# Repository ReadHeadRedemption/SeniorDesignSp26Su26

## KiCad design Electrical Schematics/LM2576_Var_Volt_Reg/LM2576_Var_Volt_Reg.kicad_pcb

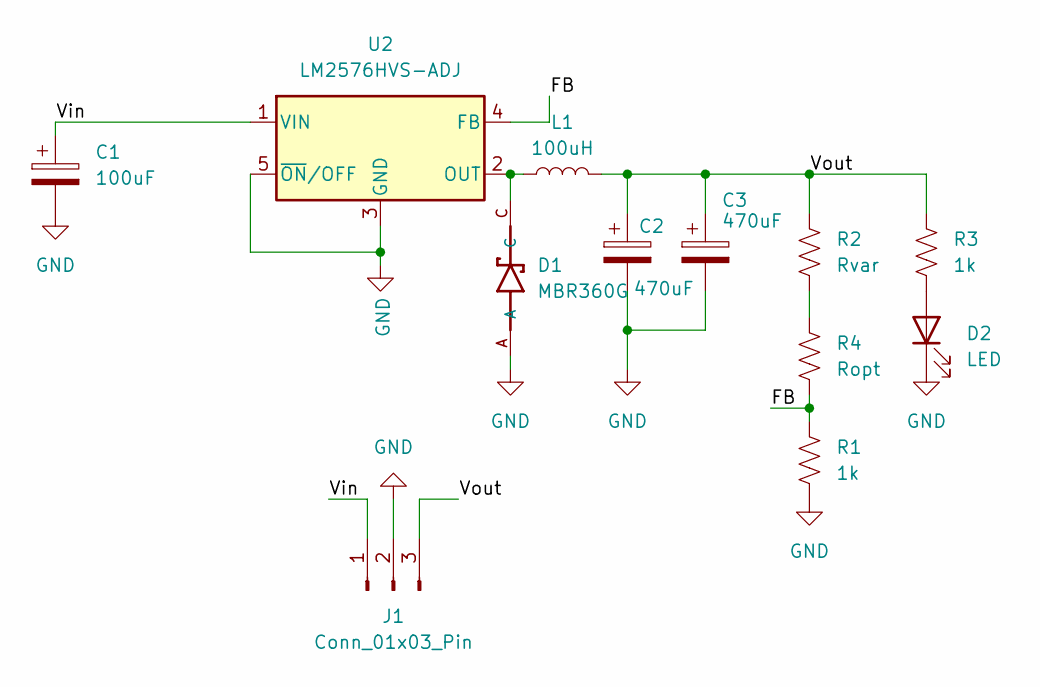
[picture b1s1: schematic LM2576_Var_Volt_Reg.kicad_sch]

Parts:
C1: 100uF; CP_Radial_D6.3mm_P2.50mm
C2, C3: 470uF; CP_Radial_D7.5mm_P2.50mm
D1: MBR360G; DIOAD950W125L840D505
D2: LED; LED_0805_2012Metric_Pad1.15x1.40mm_HandSolder
J1: Conn_01x03_Pin; PinSocket_1x03_P2.54mm_Vertical
L1: 100uH; L_Toroid_Vertical_L21.6mm_W9.5mm_P7.11mm_Pulse_C
R1: 1k; R_1206_3216Metric
R2: Rvar; R_1206_3216Metric_Pad1.30x1.75mm_HandSolder
R3: 1k; R_1206_3216Metric_Pad1.30x1.75mm_HandSolder
R4: Ropt; R_1206_3216Metric_Pad1.30x1.75mm_HandSolder
U2: LM2576HVS-ADJ; TO-263-5_TabPin3

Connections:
/FB: R1.1, R4.2, U2.4 (FB)
/Vin: C1.1, J1.1, U2.1 (VIN)
/Vout: C2.1, C3.1, J1.3, L1.2, R2.1, R3.1
GND: C1.2, C2.2, C3.2, D1.A, D2.1 (K), J1.2, R1.2, U2.3 (GND), U2.5 (~ON/OFF)
unnamed: D2.2 (A), R3.2
unnamed: R2.2, R4.1
unnamed: D1.C, L1.1, U2.2 (OUT)

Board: 2 copper layers, 12 parts (0 on the bottom side), 7 nets, no tracks yet.

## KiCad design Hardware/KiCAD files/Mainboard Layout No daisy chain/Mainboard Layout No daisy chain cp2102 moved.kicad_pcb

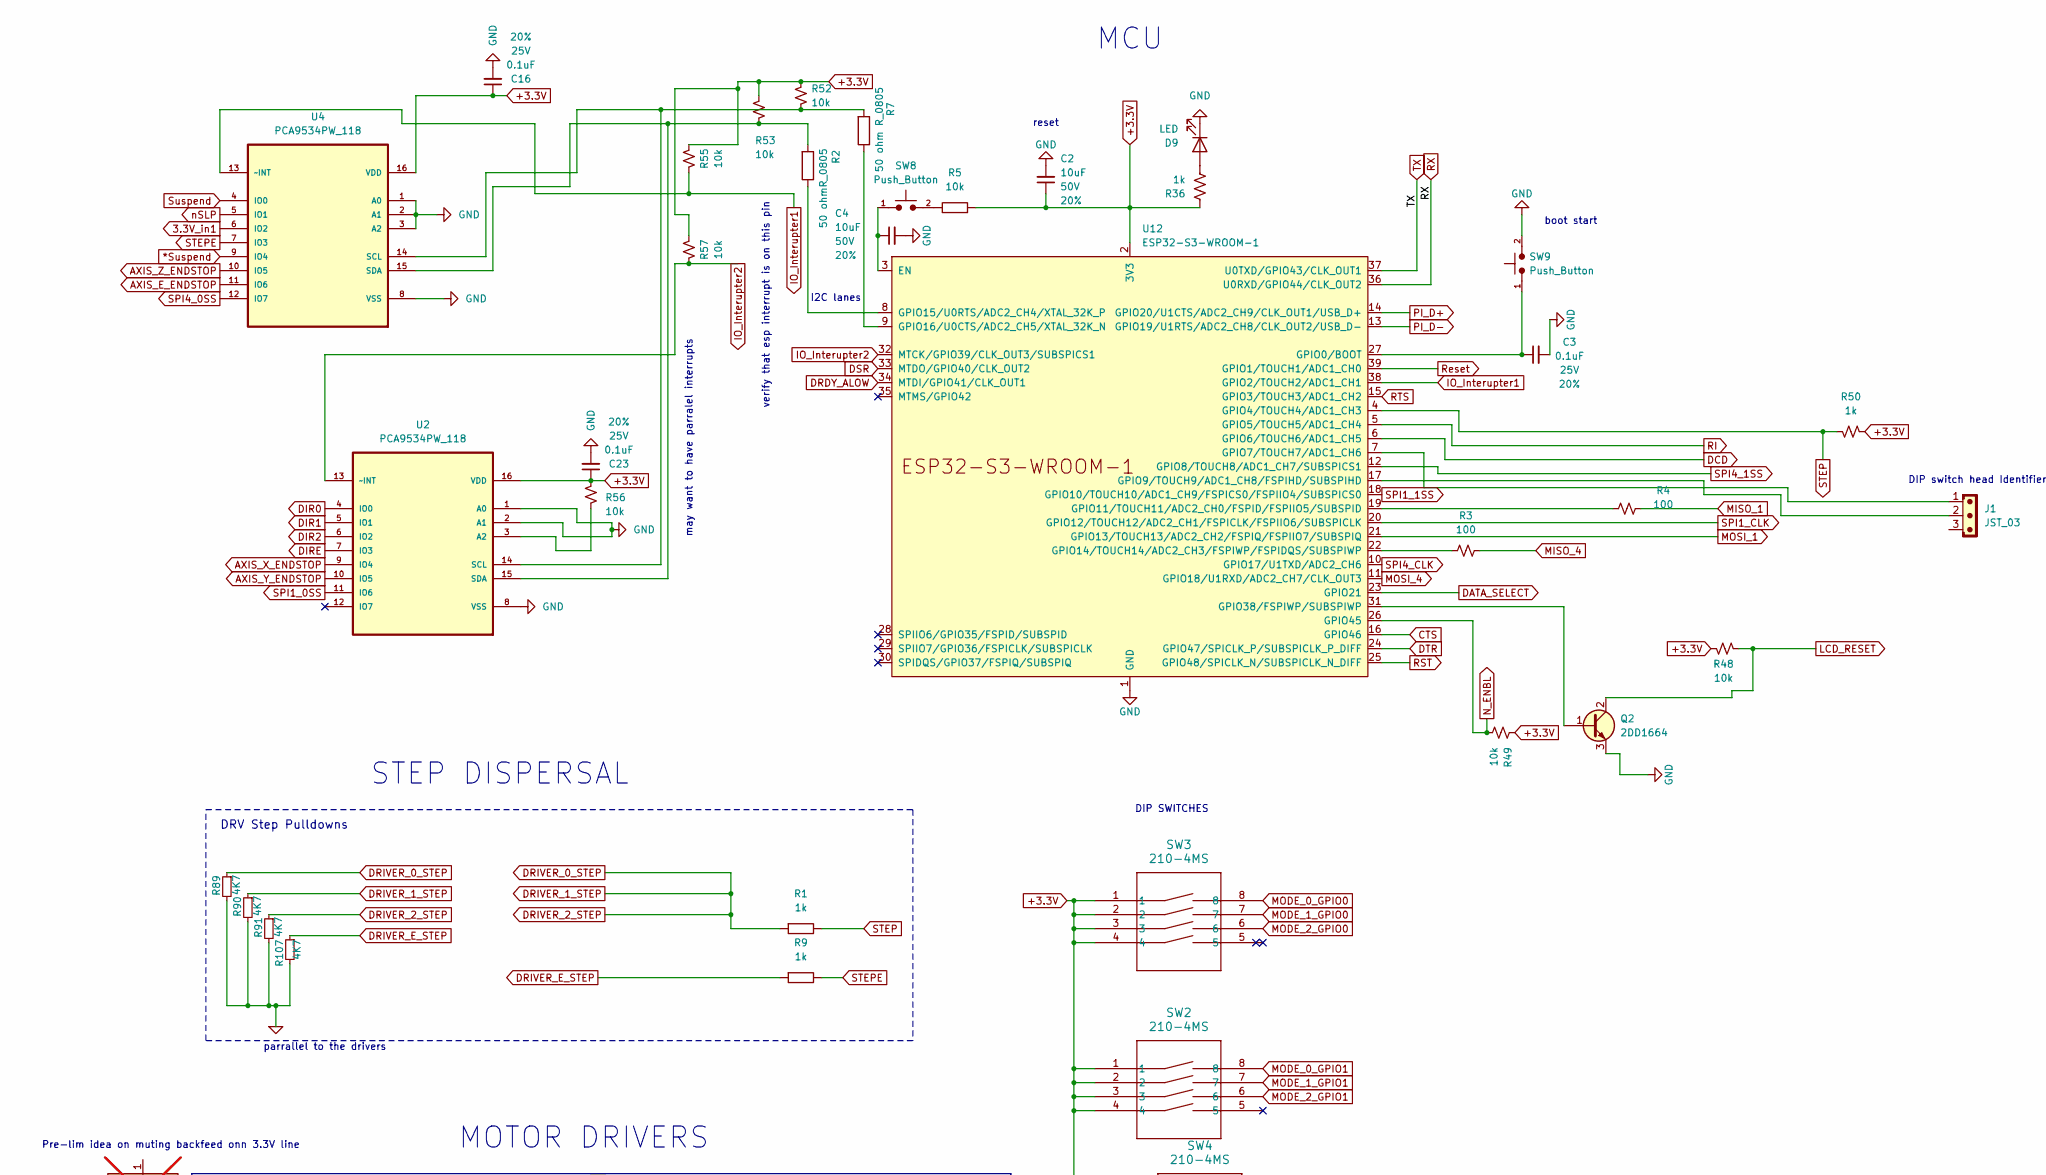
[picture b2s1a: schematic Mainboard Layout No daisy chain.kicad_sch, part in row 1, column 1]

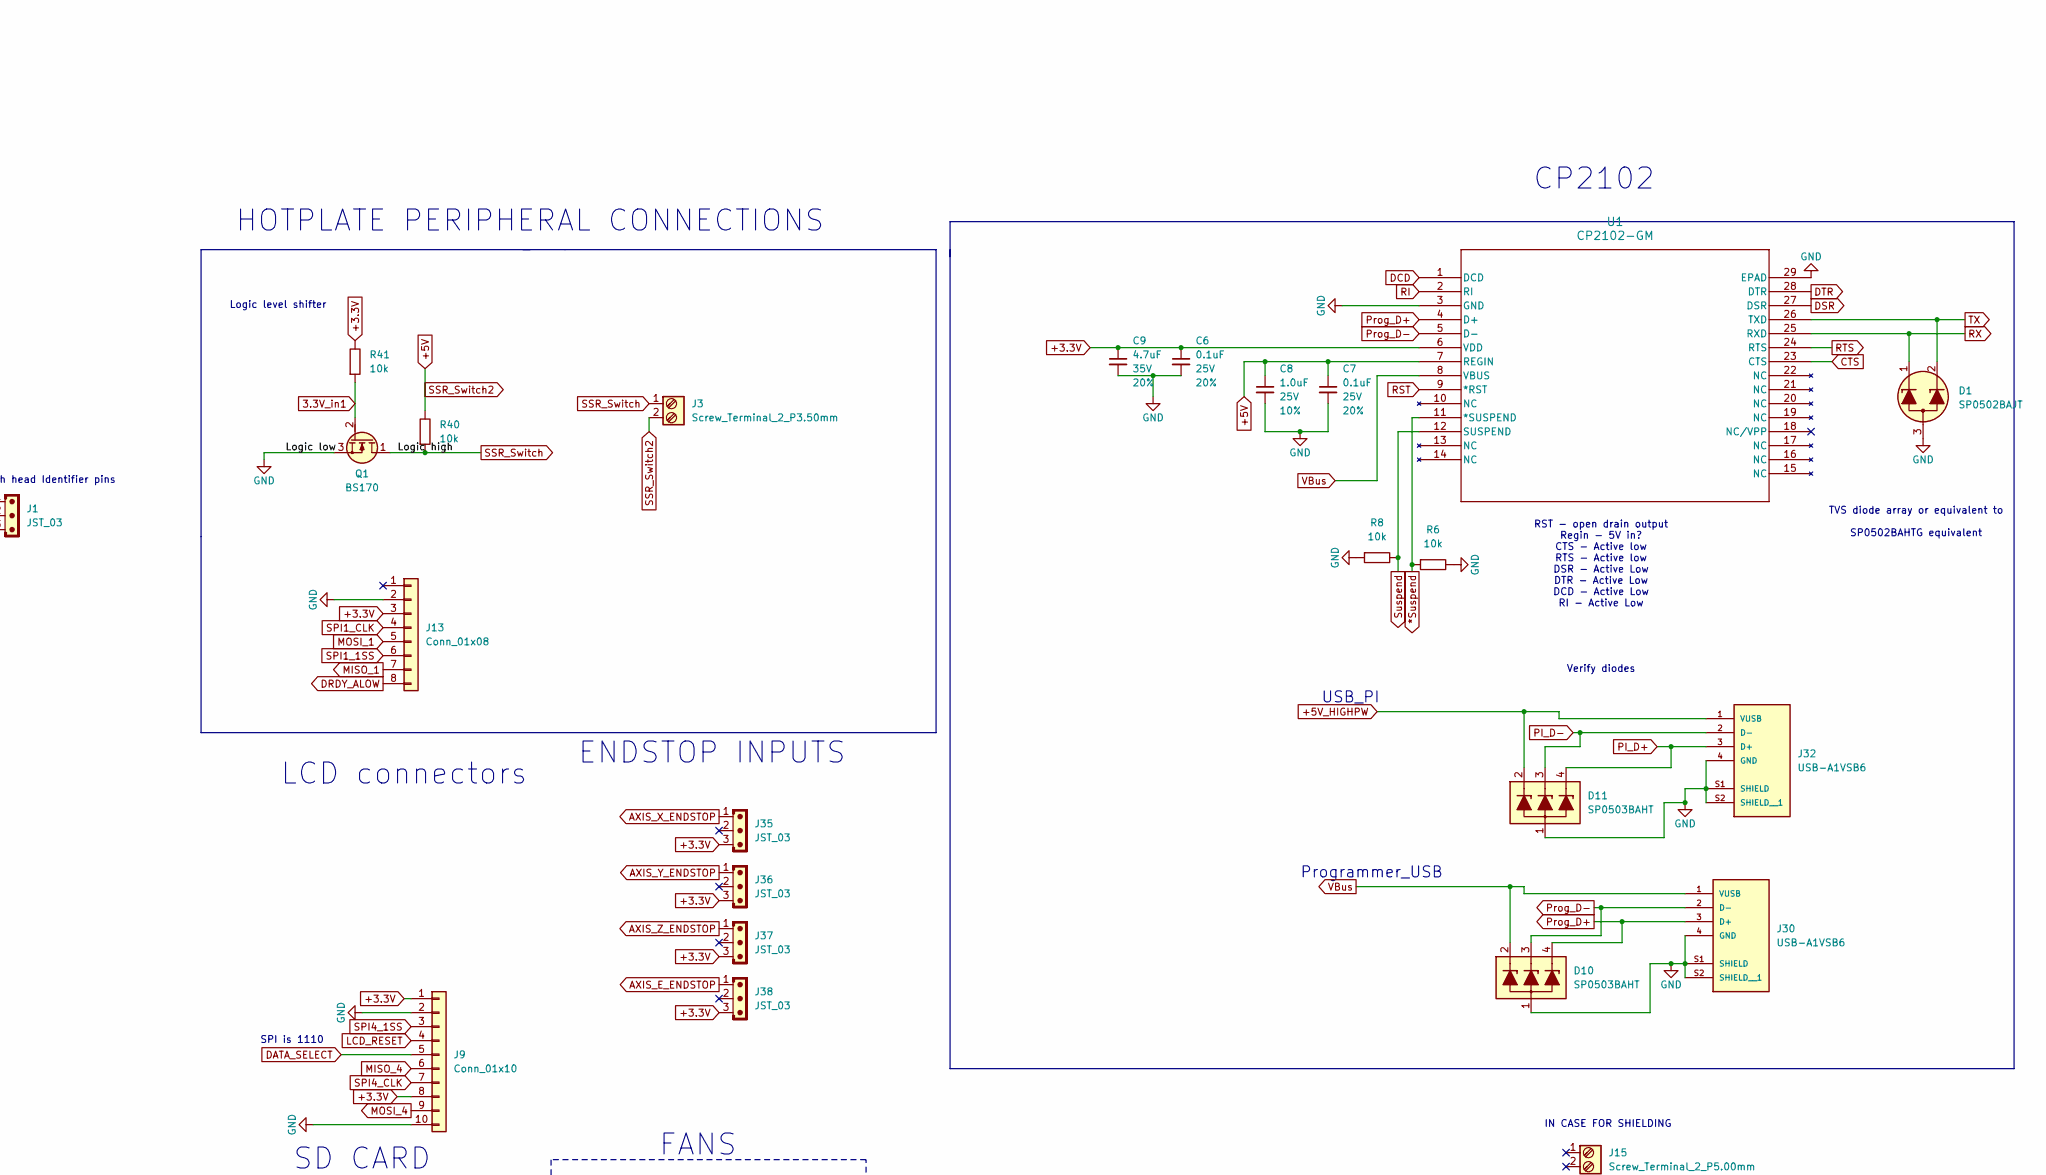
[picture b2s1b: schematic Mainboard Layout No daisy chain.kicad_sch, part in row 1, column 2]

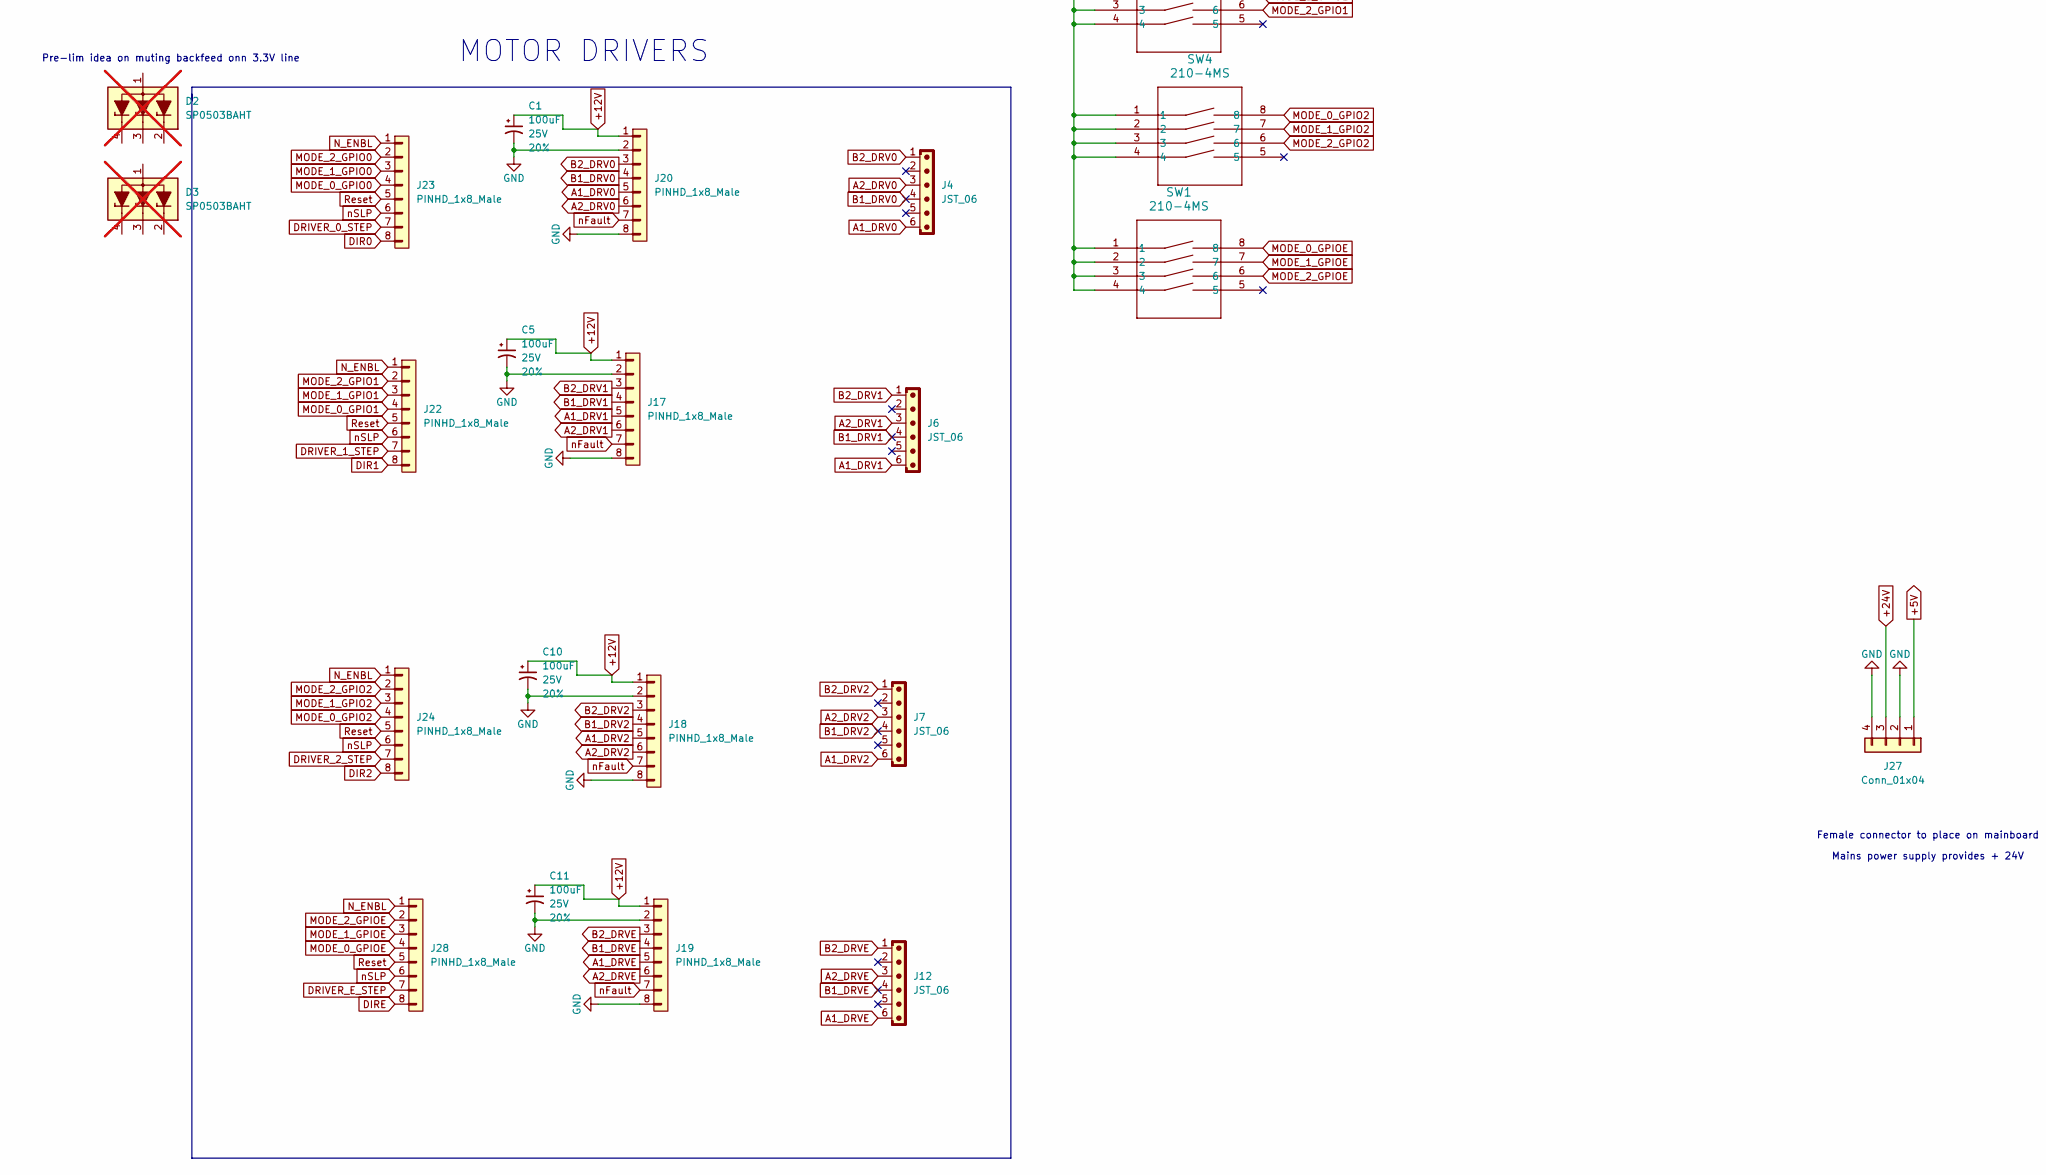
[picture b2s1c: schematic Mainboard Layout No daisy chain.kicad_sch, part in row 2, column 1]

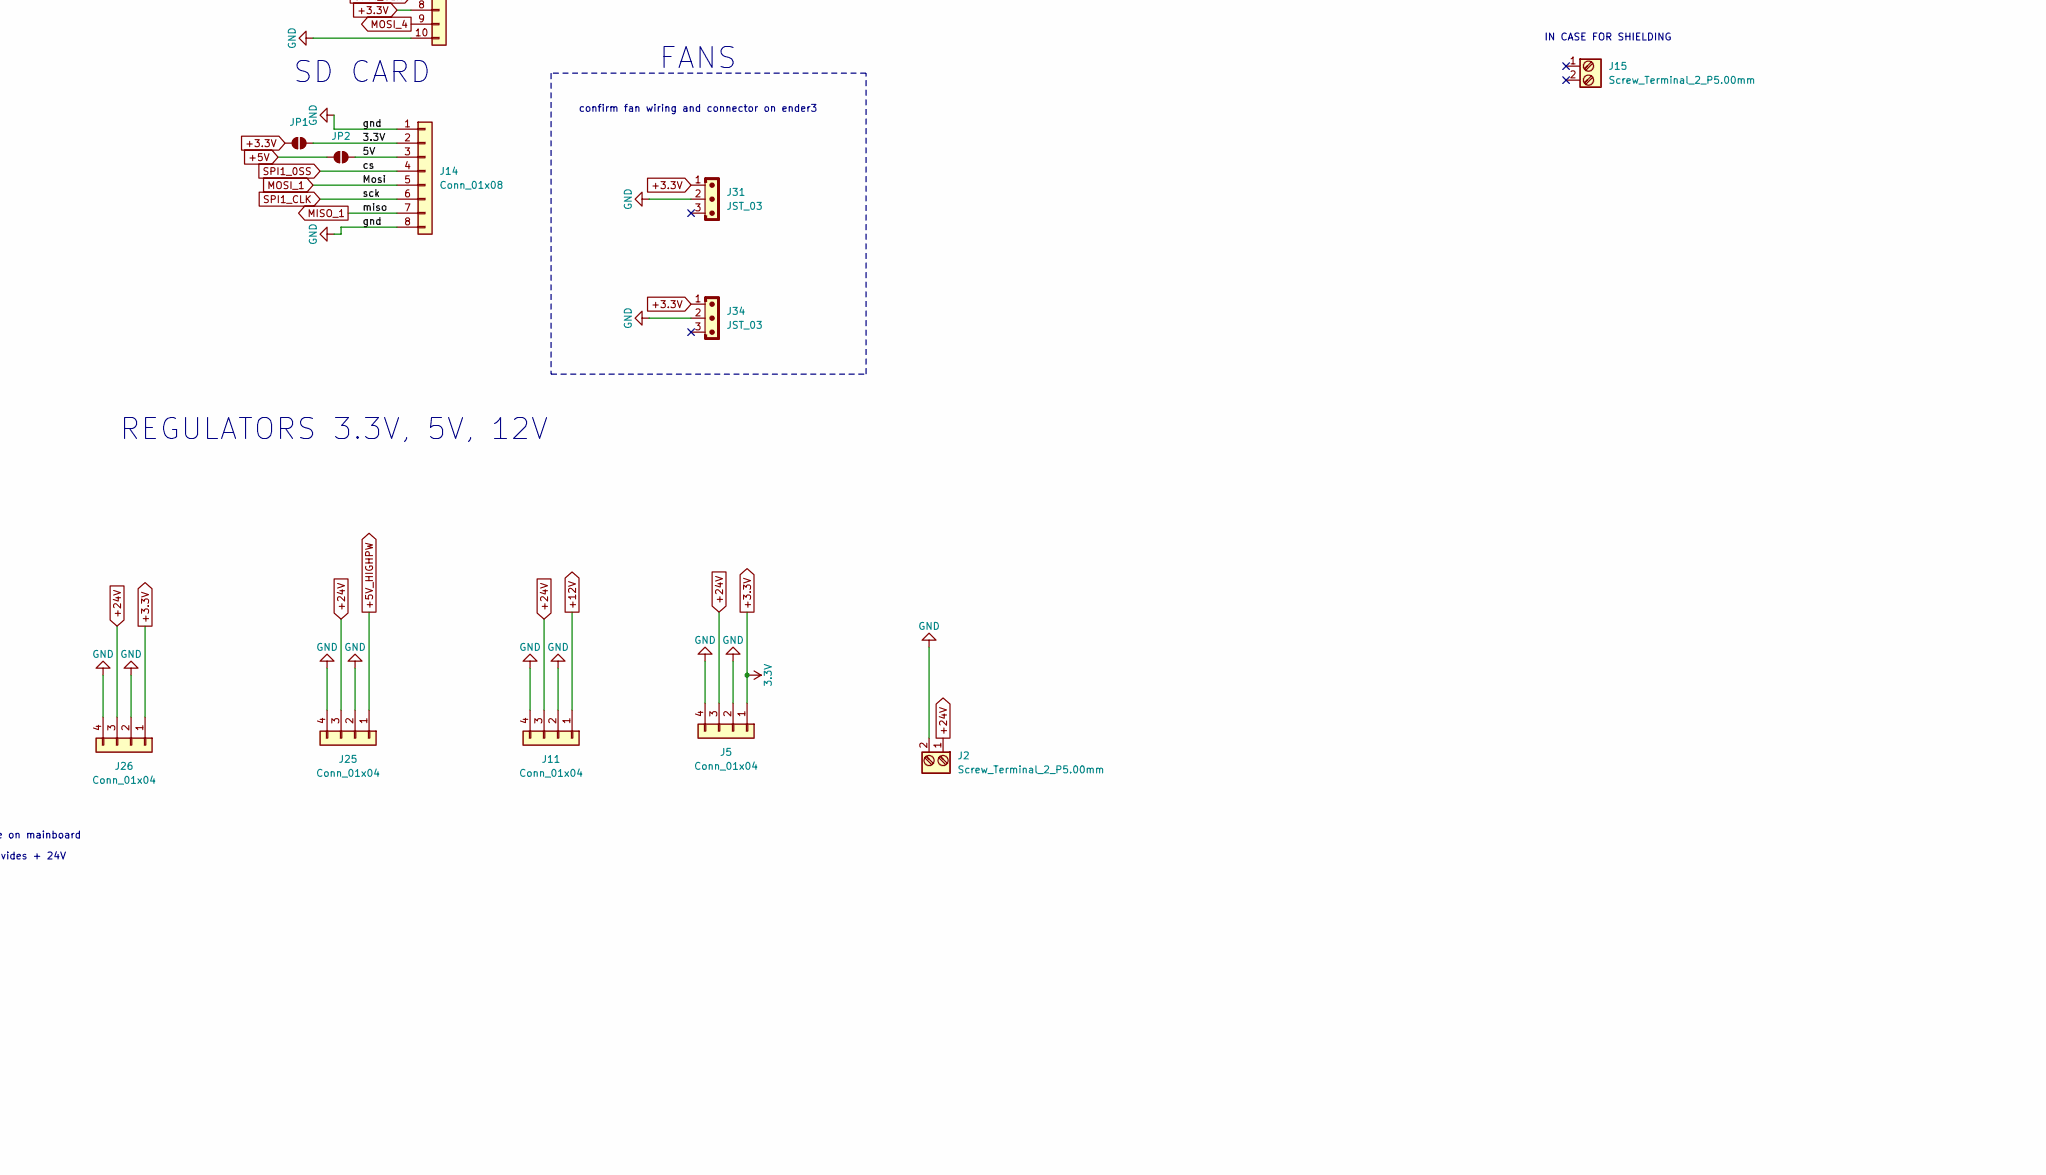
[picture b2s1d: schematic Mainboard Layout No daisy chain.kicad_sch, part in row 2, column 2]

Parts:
C1, C5, C10, C11: 100uF; Panasonic_D; Voltage 25V; Tolerance 20%
C2, C4: 10uF; C_1210_3225Metric; Voltage 50V; Tolerance 20%
C3, C6, C7: 0.1uF; C_0603_1608Metric; Voltage 25V; Tolerance 20%
C8: 1.0uF; C_0805_2012Metric; Voltage 25V; Tolerance 10%
C9: 4.7uF; C_0603_1608Metric; Voltage 35V; Tolerance 20%
C16: 0.1uF; LED_0805_2012Metric; Voltage 25V; Tolerance 20%
C23: 0.1uF; C_0805_2012Metric; Voltage 25V; Tolerance 20%
D1: SP0502BAJT; SOT-323_SC-70
D2, D3: SP0503BAHT; SOT-143; not fitted
D9: LED; LED_0603_1608Metric
D10, D11: SP0503BAHT; SOT-143
J1, J31, J34, J35, J36, J37, J38: JST_03; JST_EH_B3B-EH-A_1x03_P2.50mm_Vertical
J2, J15: Screw_Terminal_2_P5.00mm; TerminalBlock_Phoenix_PT-1,5-2-5.0-H_1x02_P5.00mm_Horizontal
J3: Screw_Terminal_2_P3.50mm; TerminalBlock_Phoenix_PT-1,5-2-3.5-H_1x02_P3.50mm_Horizontal
J4, J6, J7, J12: JST_06; JST_EH_B6B-EH-A_1x06_P2.50mm_Vertical
J5, J11, J25, J26, J27: Conn_01x04; 1x04_P2.54mm
J9: Conn_01x10; 1x10_P2.54mm
J13, J14: Conn_01x08; 1x08_P2.54mm
J17, J18, J19, J20, J22, J23, J24, J28: PINHD_1x8_Male; PinHeader_1x08_P2.54mm_Vertical
J30, J32: USB-A1VSB6; USB_A_Kycon_KUSBX-AS1N-B_Horizontal; PARTREV D
JP1, JP2: Jumper_2_NO
Q1: BS170; TO-92_Inline_Wide_DGS
Q2: 2DD1664; SOT-89-3
R1, R50: 1k; R_Axial_DIN0207_L6.3mm_D2.5mm_P10.16mm_Horizontal
R2: 50 ohmR_0805; R_0805_2012Metric
R3, R4: 100; R_0603_1608Metric
R5, R6, R8, R40, R41: 10k; R_Axial_DIN0207_L6.3mm_D2.5mm_P10.16mm_Horizontal
R7: 50 ohm R_0805; R_0805_2012Metric
R9: 1k; R_0805_2012Metric
R36: 1k; R_1206_3216Metric_Pad1.30x1.75mm_HandSolder
R48, R49: 10k; R_0603_1608Metric
R52, R53: 10k; LED_0805_2012Metric
R55, R56, R57: 10k; R_0805_2012Metric
R89, R90, R91, R107: 4K7; R_0603_1608Metric; Part Number RK73H1ETTP4701F
SW1, SW2, SW3, SW4: 210-4MS; DIP8_210-4_CTS
SW8, SW9: Push_Button; SW_PUSH_6mm
U1: CP2102-GM; QFN28_5X5_SIL
U2, U4: PCA9534PW_118; SOP65P640X110-16N; MPN PCA9534PW,118
U12: ESP32-S3-WROOM-1

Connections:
3.3V_in1: Q1.2 (G), R41.1, U4.6 (IO2)
*Suspend: R6.1, U1.11 (*SUSPEND), U4.9 (IO4)
+3.3V: C2.1, C6.1, C9.1, C16.1, C23.1, J5.1, J9.1, J9.8, J13.3, J14.2, J26.1, J31.1, J34.1, J35.3, J36.3, J37.3, J38.3, JP1.1 (A), JP1.2 (B), R5.1, R36.1, R41.2, R48.1, R49.2, R50.2, R52.2, R53.2, R55.1, R56.2, R57.1, SW1.1, SW1.2, SW1.3, SW1.4, SW2.1, SW2.2, SW2.3, SW2.4, SW3.1, SW3.2, SW3.3, SW3.4, SW4.1, SW4.2, SW4.3, SW4.4, U1.6 (VDD), U2.16 (VDD), U4.16 (VDD), U12.2 (3V3)
+5V: C7.1, C8.1, J3.2, J27.1, JP2.1 (A), R40.2, U1.7 (REGIN)
+5V_HIGHPW: D11.2 (L1), J25.1, J32.1 (VUSB)
+12V: C1.1, C5.1, C10.1, C11.1, J11.1, J17.1, J18.1, J19.1, J20.1
+24V: J2.1, J5.3, J11.3, J25.3, J26.3, J27.3
/5V: J14.3, JP2.2 (B)
A1_DRV0: J4.6, J20.5
A1_DRV1: J6.6, J17.5
A1_DRV2: J7.6, J18.5
A1_DRVE: J12.6, J19.5
A2_DRV0: J4.3, J20.6
A2_DRV1: J6.3, J17.6
A2_DRV2: J7.3, J18.6
A2_DRVE: J12.3, J19.6
AXIS_E_ENDSTOP: J38.1, U4.11 (IO6)
AXIS_X_ENDSTOP: J35.1, U2.9 (IO4)
AXIS_Y_ENDSTOP: J36.1, U2.10 (IO5)
AXIS_Z_ENDSTOP: J37.1, U4.10 (IO5)
B1_DRV0: J4.4, J20.4
B1_DRV1: J6.4, J17.4
B1_DRV2: J7.4, J18.4
B1_DRVE: J12.4, J19.4
B2_DRV0: J4.1, J20.3
B2_DRV1: J6.1, J17.3
B2_DRV2: J7.1, J18.3
B2_DRVE: J12.1, J19.3
CTS: U1.23 (CTS), U12.16 (GPIO46)
DATA_SELECT: J9.5, U12.23 (GPIO21)
DCD: U1.1 (DCD), U12.6 (GPIO6/TOUCH6/ADC1_CH5)
DIR0: J23.8, U2.4 (IO0)
DIR1: J22.8, U2.5 (IO1)
DIR2: J24.8, U2.6 (IO2)
DIRE: J28.8, U2.7 (IO3)
DRDY_ALOW: J13.8, U12.34 (MTDI/GPIO41/CLK_OUT1)
DRIVER_0_STEP: J22.7, J23.7, J24.7, R1.1, R89.1, R90.1, R91.1
DRIVER_E_STEP: J28.7, R9.1, R107.1
DSR: U1.27 (DSR), U12.33 (MTDO/GPIO40/CLK_OUT2)
DTR: U1.28 (DTR), U12.24 (GPIO47/SPICLK_P/SUBSPICLK_P_DIFF)
GND: C1.2, C2.2, C3.2, C4.2, C5.2, C6.2, C7.2, C8.2, C9.2, C10.2, C11.2, C16.2, C23.2, D1.3 (A), D9.1 (K), D10.1 (VN), D11.1 (VN), J2.2, J5.2, J5.4, J9.2, J9.10, J11.2, J11.4, J13.2, J14.1, J14.8, J17.2, J17.8, J18.2, J18.8, J19.2, J19.8, J20.2, J20.8, J25.2, J25.4, J26.2, J26.4, J27.2, J27.4, J30.4 (GND), J30.S1 (SHIELD), J30.S2 (SHIELD__1), J31.2, J32.4 (GND), J32.S1 (SHIELD), J32.S2 (SHIELD__1), J34.2, Q1.3 (S), Q2.3 (E), R6.2, R8.1, R89.2, R90.2, R91.2, R107.2, SW9.2, U1.3 (GND), U1.29 (EPAD), U2.1 (A0), U2.2 (A1), U2.8 (VSS), U4.1 (A0), U4.2 (A1), U4.3 (A2), U4.8 (VSS), U12.1 (GND), U12.40 (GND), U12.41 (GND)
IO_Interupter1: R55.2, U4.13 (~INT), U12.38 (GPIO2/TOUCH2/ADC1_CH1)
IO_Interupter2: R57.2, U2.13 (~INT), U12.32 (MTCK/GPIO39/CLK_OUT3/SUBSPICS1)
LCD_RESET: J9.4, Q2.2 (C), R48.2
MISO_1: J13.7, J14.7, R4.2
MISO_4: J9.6, R3.2
MODE_0_GPIO0: J23.4, SW3.8
MODE_0_GPIO1: J22.4, SW2.8
MODE_0_GPIO2: J24.4, SW4.8
MODE_0_GPIOE: J28.4, SW1.8
MODE_1_GPIO0: J23.3, SW3.7
MODE_1_GPIO1: J22.3, SW2.7
MODE_1_GPIO2: J24.3, SW4.7
MODE_1_GPIOE: J28.3, SW1.7
MODE_2_GPIO0: J23.2, SW3.6
MODE_2_GPIO1: J22.2, SW2.6
MODE_2_GPIO2: J24.2, SW4.6
MODE_2_GPIOE: J28.2, SW1.6
MOSI_1: J13.5, J14.5, U12.21 (GPIO13/TOUCH13/ADC2_CH2/FSPIQ/FSPIIO7/S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)
MOSI_4: J9.9, U12.11 (GPIO18/U1RXD/ADC2_CH7/CLK_OUT3)
N_ENBL: J22.1, J23.1, J24.1, J28.1, R49.1, U12.26 (GPIO45)
unnamed: D9.2 (A), R36.2
unnamed: Q2.1 (B), U12.31 (GPIO38/FSPIWP/SUBSPIWP)
unnamed: R5.2, SW8.2
unnamed: R56.1, U2.3 (A2)
unnamed: R7.1, R52.1, U2.14 (SCL), U4.14 (SCL)
unnamed: R2.1, R53.1, U2.15 (SDA), U4.15 (SDA)
unnamed: C4.1, SW8.1, U12.3 (EN)
unnamed: C3.1, SW9.1, U12.27 (GPIO0/BOOT)
unnamed: J1.1, U12.7 (GPIO7/TOUCH7/ADC1_CH6)
unnamed: J1.2, U12.17 (GPIO9/TOUCH9/ADC1_CH8/FSPIHD/SUBSPIHD)
unnamed: R4.1, U12.19 (GPIO11/TOUCH11/ADC2_CH0/FSPID/FSPIIO5/S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)
unnamed: R3.1, U12.22 (GPIO14/TOUCH14/ADC2_CH3/FSPIWP/FSPIDQS/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)
unnamed: R2.2, U12.8 (GPIO15/U0RTS/ADC2_CH4/XTAL_32K_P)
unnamed: R7.2, U12.9 (GPIO16/U0CTS/ADC2_CH5/XTAL_32K_N)
PI_D+: D11.4 (L3), J32.3 (D+), U12.14 (GPIO20/U1CTS/ADC2_CH9/CLK_OUT1/USB_D+)
PI_D-: D11.3 (L2), J32.2 (D-), U12.13 (GPIO19/U1RTS/ADC2_CH8/CLK_OUT2/USB_D-)
Prog_D+: D10.4 (L3), J30.3 (D+), U1.4 (D+)
Prog_D-: D10.3 (L2), J30.2 (D-), U1.5 (D-)
RI: U1.2 (RI), U12.5 (GPIO5/TOUCH5/ADC1_CH4)
RST: U1.9 (*RST), U12.25 (GPIO48/SPICLK_N/SUBSPICLK_N_DIFF)
RTS: U1.24 (RTS), U12.15 (GPIO3/TOUCH3/ADC1_CH2)
RX: D1.1 (K1), U1.25 (RXD), U12.36 (U0RXD/GPIO44/CLK_OUT2)
Reset: J22.5, J23.5, J24.5, J28.5, U12.39 (GPIO1/TOUCH1/ADC1_CH0)
SPI1_0SS: J14.4, U2.11 (IO6)
SPI1_1SS: J13.6, U12.18 (GPIO10/TOUCH10/ADC1_CH9/FSPICS0/FSPIIO4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)
SPI1_CLK: J13.4, J14.6, U12.20 (GPIO12/TOUCH12/ADC2_CH1/FSPICLK/FSPIIO6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)
SPI4_0SS: U4.12 (IO7)
SPI4_1SS: J9.3, U12.12 (GPIO8/TOUCH8/ADC1_CH7/SUBSPICS1)
SPI4_CLK: J9.7, U12.10 (GPIO17/U1TXD/ADC2_CH6)
SSR_Switch: J3.1, Q1.1 (D), R40.1
STEP: R1.2, R50.1, U12.4 (GPIO4/TOUCH4/ADC1_CH3)
STEPE: R9.2, U4.7 (IO3)
Suspend: R8.2, U1.12 (SUSPEND), U4.4 (IO0)
TX: D1.2 (K2), U1.26 (TXD), U12.37 (U0TXD/GPIO43/CLK_OUT1)
VBus: D10.2 (L1), J30.1 (VUSB), U1.8 (VBUS)
nFault: J17.7, J18.7, J19.7, J20.7
nSLP: J22.6, J23.6, J24.6, J28.6, U4.5 (IO1)

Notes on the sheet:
verify that esp interrupt is on this pin
USB_PI
Pre-lim idea on muting backfeed onn 3.3V line
MCU
REGULATORS 3.3V, 5V, 12V
IN CASE FOR SHIELDING
Female connector to place on mainboard
RST - open drain output Regin - 5V in? CTS - Active low RTS - Active low DSR - Active Low DTR - Active Low DCD - Active Low RI - Active Low
Mains power supply provides + 24V
DIP SWITCHES
SD CARD
HOTPLATE PERIPHERAL CONNECTIONS
SPI is 1110
boot start
confirm fan wiring and connector on ender3
Programmer_USB
FANS
TVS diode array or equivalent to SP0502BAHTG equivalent
Logic level shifter
Verify diodes
reset
may want to have parralel interrupts
LCD connectors
I2C lanes
DIP switch head Identifier pins
CP2102
parrallel to the drivers
MOTOR DRIVERS
DRV Step Pulldowns
STEP DISPERSAL
ENDSTOP INPUTS

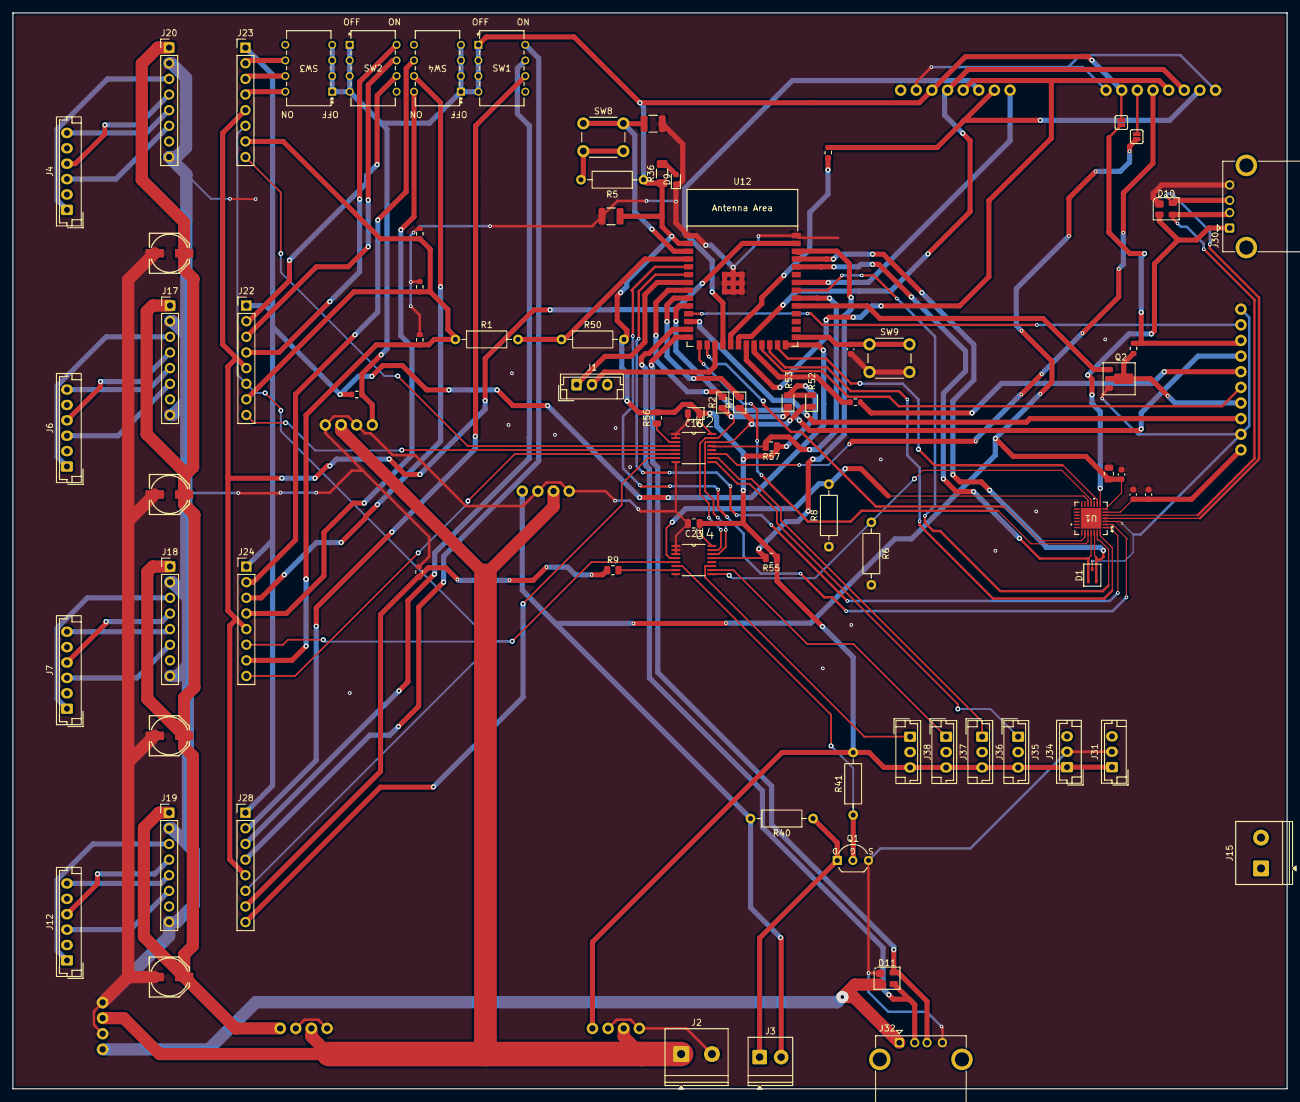
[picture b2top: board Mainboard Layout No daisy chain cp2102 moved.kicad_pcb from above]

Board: 2 copper layers, 207.0 x 174.8 mm, 87 parts (0 on the bottom side), 97 nets.

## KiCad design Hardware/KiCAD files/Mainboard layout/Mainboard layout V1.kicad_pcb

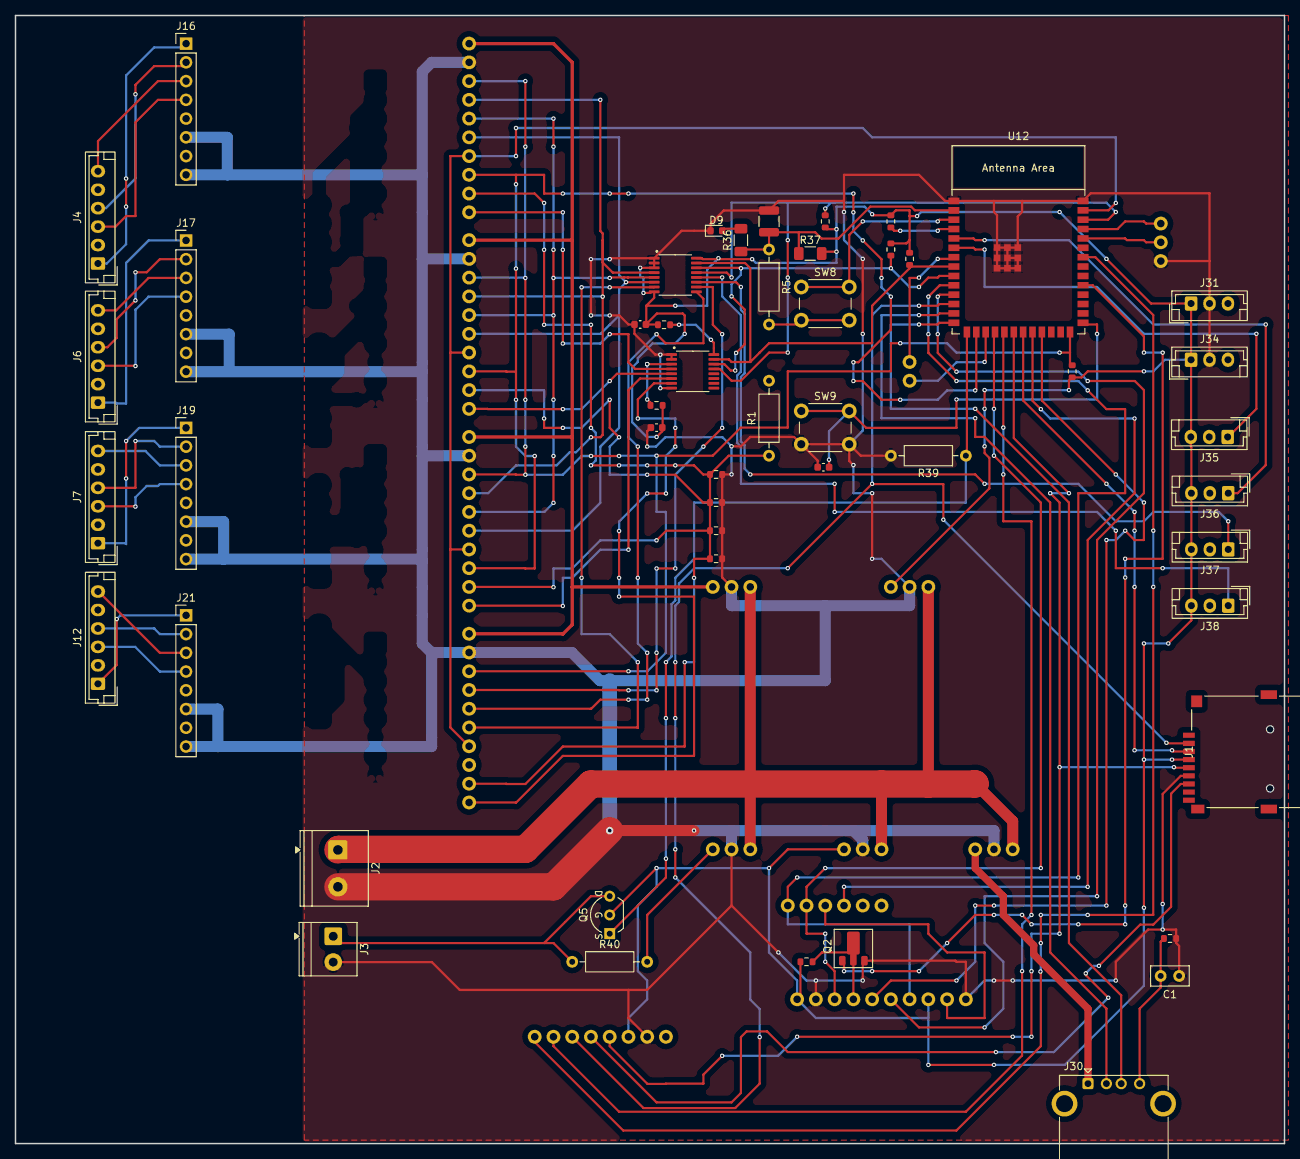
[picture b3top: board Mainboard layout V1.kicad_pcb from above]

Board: 2 copper layers, 172.0 x 152.9 mm, 64 parts (0 on the bottom side), 75 nets.

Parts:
C1: 1nF_Ceramic; C_Disc_D5.0mm_W2.5mm_P2.50mm
C2: 10uF; C_1210_3225Metric
C3, C16, C23: 0.1uF; C_0603_1608Metric
D9: LED; LED_0603_1608Metric
J1: MSD-1-A; CONN9_MSD-1_CUD
J2: Screw_Terminal_2_P5.00mm; TerminalBlock_Phoenix_PT-1,5-2-5.0-H_1x02_P5.00mm_Horizontal
J3: Screw_Terminal_2_P3.50mm; TerminalBlock_Phoenix_PT-1,5-2-3.5-H_1x02_P3.50mm_Horizontal
J4, J6, J7, J12: JST_06; JST_EH_B6B-EH-A_1x06_P2.50mm_Vertical
J8: Conn_01x06; 1x06_P2.54mm
J9, J18, J20, J23, J24: Conn_01x10; 1x10_P2.54mm
J10: Conn_01x02; 1x02_P2.54mm
J11, J14, J15, J22, J28, J29: Conn_01x03; 1x03_P2.54mm
J13: Conn_01x08; 1x08_P2.54mm
J16, J17, J19, J21: PINHD_1x8_Male; PinHeader_1x08_P2.54mm_Vertical
J30: USB-A1VSB6; USB_A_Kycon_KUSBX-AS1N-B_Horizontal
J31, J34, J35, J36, J37, J38: JST_03; JST_EH_B3B-EH-A_1x03_P2.50mm_Vertical
Q2: 2DD1664; SOT-89-3
Q5: 2N7000; TO-92_Inline_Wide_SGD
R1: 1k; R_Axial_DIN0207_L6.3mm_D2.5mm_P10.16mm_Horizontal
R5, R39: 10k; R_Axial_DIN0207_L6.3mm_D2.5mm_P10.16mm_Horizontal
R6: 1M; R_0603_1608Metric
R36, R37: 1k; R_1206_3216Metric_Pad1.30x1.75mm_HandSolder
R40: 100k; R_Axial_DIN0207_L6.3mm_D2.5mm_P10.16mm_Horizontal
R48, R49, R50, R52, R53, R54, R55, R56: 10k; R_0603_1608Metric
R89, R90, R91, R107: 4K7; R_0603_1608Metric
SW8, SW9: Push_Button; SW_PUSH_6mm
U3, U5: PCA9534PW; TSSOP-16_4.4x5mm_P0.65mm
U12: ESP32-S3-WROOM-1

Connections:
3.3V_in1: Q5.1 (S), R39.1, U12.15 (GPIO3/TOUCH3/ADC1_CH2)
+3.3V: C16.1, C23.1, J1.4 (VDD), J9.1, J9.8, J13.3, J15.1, J22.1, J31.1, J34.1, J35.3, J36.3, J37.3, J38.3, Q5.2 (G), R37.2, R48.1, R49.2, R50.2, R52.2, R53.2, R54.2, R55.1, R56.2, U3.16 (VDD)
+5V: J14.1, R40.2
+5V_HIGHPW: J28.1, J30.1 (VUSB)
+12V: J18.10, J20.10, J23.10, J24.10, J29.1
+24V: J2.1, J14.3, J15.3, J22.3, J28.3, J29.3
/RX: J11.2, U12.36 (U0RXD/GPIO44/CLK_OUT2)
/TX: J11.1, U12.37 (U0TXD/GPIO43/CLK_OUT1)
A1_DRV0: J4.6, J16.3
A1_DRV1: J6.6, J17.3
A1_DRV2: J7.6, J19.3
A1_DRVE: J12.6, J21.3
A2_DRV0: J4.3, J16.4
A2_DRV1: J6.3, J17.4
A2_DRV2: J7.3, J19.4
A2_DRVE: J12.3, J21.4
AXIS_E_ENDSTOP: J38.1, U3.12 (IO7)
AXIS_X_ENDSTOP: J35.1, U12.6 (GPIO6/TOUCH6/ADC1_CH5)
AXIS_Y_ENDSTOP: J36.1, U12.5 (GPIO5/TOUCH5/ADC1_CH4)
AXIS_Z_ENDSTOP: J37.1, U3.11 (IO6)
B1_DRV0: J4.4, J16.2
B1_DRV1: J6.4, J17.2
B1_DRV2: J7.4, J19.2
B1_DRVE: J12.4, J21.2
B2_DRV0: J4.1, J16.1
B2_DRV1: J6.1, J17.1
B2_DRV2: J7.1, J19.1
B2_DRVE: J12.1, J21.1
CHAINL0_MISO_1: J1.7 (DAT0), J13.5
CHAINL0_MISO_4: J8.3, J9.9
D+: J30.3 (D+), U12.14 (GPIO20/U1CTS/ADC2_CH9/CLK_OUT1/USB_D+)
D-: J30.2 (D-), U12.13 (GPIO19/U1RTS/ADC2_CH8/CLK_OUT2/USB_D-)
DATA_SELECT: J9.5, U12.23 (GPIO21)
DIR0: J18.1, U5.4 (IO0)
DIR1: J20.1, U5.5 (IO1)
DIR2: J23.1, U5.6 (IO2)
DIRE: J24.1, U5.7 (IO3)
DRDY_ALOW: J13.8, U12.34 (MTDI/GPIO41/CLK_OUT1)
DRIVER_0_STEP: J18.2, J20.2, J23.2, J24.2, R1.1, R89.1, R90.1, R91.1, R107.1
GND: C1.1, C2.2, C3.2, C16.2, C23.2, D9.1 (K), J1.6 (VSS), J2.2, J3.2, J9.2, J9.10, J11.3, J13.2, J14.2, J15.2, J16.6, J16.8, J17.6, J17.8, J18.9, J19.6, J19.8, J20.9, J21.6, J21.8, J22.2, J23.9, J24.9, J28.2, J29.2, J31.2, J34.2, Q2.3 (E), R6.1, R39.2, R89.2, R90.2, R91.2, R107.2, SW9.2, U3.1 (A0), U3.2 (A1), U3.3 (A2), U3.8 (VSS), U5.1 (A0), U5.2 (A1), U5.8 (VSS), U12.1 (GND), U12.40 (GND), U12.41 (GND)
IO_Interupter: R55.2, U3.13 (~INT), U5.13 (~INT), U12.38 (GPIO2/TOUCH2/ADC1_CH1)
LCD_RESET: J9.4, Q2.2 (C), R48.2
MISO_1: J13.7, U12.19 (GPIO11/TOUCH11/ADC2_CH0/FSPID/FSPIIO5/S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)
MISO_4: J8.4, U12.22 (GPIO14/TOUCH14/ADC2_CH3/FSPIWP/FSPIDQS/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)
MODE_0_GPIO: J18.7, J20.7, J23.7, U3.4 (IO0)
MODE_0_GPIOE: J24.7, U3.10 (IO5)
MODE_1_GPIO: J18.6, J20.6, J23.6, U3.5 (IO1)
MODE_1_GPIOE: J24.6, U3.9 (IO4)
MODE_2_GPIO: J18.5, J20.5, J23.5, U3.6 (IO2)
MODE_2_GPIOE: J24.5, U3.7 (IO3)
MOSI_1: J1.3 (CMD), U12.21 (GPIO13/TOUCH13/ADC2_CH2/FSPIQ/FSPIIO7/S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)
MOSI_4: J9.6, U12.11 (GPIO18/U1RXD/ADC2_CH7/CLK_OUT3)
N_ENBL: J18.8, J20.8, J23.8, J24.8, R49.1, U12.26 (GPIO45)
unnamed: D9.2 (A), R36.2
unnamed: J10.1, U12.7 (GPIO7/TOUCH7/ADC1_CH6)
unnamed: J10.2, U12.17 (GPIO9/TOUCH9/ADC1_CH8/FSPIHD/SUBSPIHD)
unnamed: C1.2, J30.4 (GND), R6.2
unnamed: Q2.1 (B), U12.31 (GPIO38/FSPIWP/SUBSPIWP)
unnamed: R5.2, SW8.2
unnamed: R56.1, U5.3 (A2)
unnamed: R54.1, U5.16 (VDD)
unnamed: C2.1, R5.1, R36.1, R37.1, U12.2 (3V3)
unnamed: SW8.1, U12.3 (EN)
unnamed: C3.1, SW9.1, U12.27 (GPIO0/BOOT)
unnamed: R53.1, U3.15 (SDA), U5.15 (SDA), U12.8 (GPIO15/U0RTS/ADC2_CH4/XTAL_32K_P)
unnamed: R52.1, U3.14 (SCL), U5.14 (SCL), U12.9 (GPIO16/U0CTS/ADC2_CH5/XTAL_32K_N)
Reset: J18.4, J20.4, J23.4, J24.4, U12.39 (GPIO1/TOUCH1/ADC1_CH0)
SPI1_CLK: J1.5 (CLK), J13.4, U12.20 (GPIO12/TOUCH12/ADC2_CH1/FSPICLK/FSPIIO6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)
SPI1_CS: J1.2 (CD/DAT3), J13.6, U12.12 (GPIO8/TOUCH8/ADC1_CH7/SUBSPICS1)
SPI4_CLK: J8.1, J9.7, U12.10 (GPIO17/U1TXD/ADC2_CH6)
SPI4_CS: J8.2, J9.3, U12.18 (GPIO10/TOUCH10/ADC1_CH9/FSPICS0/FSPIIO4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)
SSR_Switch: J3.1, Q5.3 (D), R40.1
Step: R50.1, U12.4 (GPIO4/TOUCH4/ADC1_CH3)
nFault: J16.5, J17.5, J19.5, J21.5
nSLP: J18.3, J20.3, J23.3, J24.3, U12.16 (GPIO46)
